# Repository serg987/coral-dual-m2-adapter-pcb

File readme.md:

# Dual Coral TPU m.2 E key to NVME m.2 M key adapter

## Overview

Simple adapter to install up to 2 dual Coral TPU modules in m.2 E key format to m.2 M key 2280 nvme slot.
Single E key Coral modules and a combination of single and dual ones should work as well.
The idea was to create a simple and affordable adapter on a two-layer PCB that can be soldered without 
any special equipment and professional soldering skills. The drawback is that it relies on some specific 
hardware and components, but they are still relatively easy to purchase. Also it goes out of m.2 2280 slot dimensions
by 8 mm on the side of the secure screw.

Third-party references: M2 E-Key slot KiCad symbol and the footprint are taken from 
https://github.com/CRImier/MyKiCad/tree/master/Laptop%20mods with some adjustments.

## Get the PCB

You can order PCB from PBCway.com via this 
[link](https://www.pcbway.com/project/shareproject/Dual_Coral_TPU_m_2_E_key_to_NVME_m_2_M_key_adapter_e422809f.html). 
Buying it from PCBway (should be around $10 including delivery to the US) you would support the Author in his 
future development.

### Gerbers

Gerber files are not provided. To get them, open the Kicad project and export them. 

## Hardware and schematics

The main part is m.2 M key expansion board based on the ASM1184E chip. It splits 1 PCIE lane into 4 single ones. It 
affects the speed, but for this specific application, the PCIE speed affects only a little. The adapter is connected to 
this board with 4 USB-3 Type A male connectors. The adapter has its power supply and needs an external power source of
5-12V. The adapter's PCB is installed above the expansion board as a sandwich, having an overall height of about 25 mm 
without Coral heat sink. The dimensions allow installation into the Dell Micro 50XX/70XX case, but without a heatsink, 
so it may have issues with heat dissipation there. The author used a Chatreey iT12 mini-pc which is available on 
Aliexpress without its bottom cover. The adapter hangs over m.2 2280 secure screw by around 8 mm. But in most cases, 
it should not be an issue.

An example of the adapter installed in the Dell Micro case (here and in some other pictures is the first version of the 
adapter that has a slightly different layout, but the same dimensions):

An example of the adapter installed in Chatreey iT12 mini-pc case:

### PCIE connections

Pretty straightforward. A few lanes are swapped to make it easier to trace the PCB. CLKREQ# pins are connected to
pull-up resistors. PERST# pins are combined as the AS1184 board has them all connected. PEWAKE# pins are not used.

### Power supply

ASM1184 datasheet is not available, but it heats up very well suspiciously consuming a significant current.
4 TPUs may consume around 6W, so it may be not enough for a m2 socket to handle that power. That's why a
separate power supply is introduced for Coral modules. It can be supplied from a 5 to 12 V power source.
It is based on the FR9889 chip and has the following schematics:

According to datasheet, R4 + R5 both should be 26.2 kOhm, but it can be something in between of 25.5 to 27.0 kOhm

The full schematics in PDF is [here](media/schematics.pdf) 

### Heat dissipation

ASM1184 board comes with its heatsink. Four Coral TPUs are heated up pretty quickly, so it is _necessary_ to have a 
heatsink for them as well. The author used a standard m2 SSD heatsink with a 1.0 mm thermal pad were secured by 2 
rubber rings.

## PCB layouts

Front:

Bottom:

Again, you can order PCBs 
[here](https://www.pcbway.com/project/shareproject/Dual_Coral_TPU_m_2_E_key_to_NVME_m_2_M_key_adapter_e422809f.html)

## Parts and materials

| Part                                     | Picture                                                                                              | Link to buy                                                                                                                                                                                                                                                                                    | Comments                                                                                                                                                         |
|------------------------------------------|------------------------------------------------------------------------------------------------------|------------------------------------------------------------------------------------------------------------------------------------------------------------------------------------------------------------------------------------------------------------------------------------------------|------------------------------------------------------------------------------------------------------------------------------------------------------------------|
| m.2 M key PCIE expansion card            |                        | [Aliexpress1](https://www.aliexpress.us/item/3256806084552405.html) <br/>[Aliexpress2](https://www.aliexpress.us/item/3256804686887041.html) <br/>[Aliexpress3](https://www.aliexpress.us/item/3256805414546446.html)<br/> [Aliexpress4](https://www.aliexpress.us/item/3256804977336000.html) | Many of them, search by 'ASM1184 m2' on other marketplaces                                                                                                       |
| USB3 type A through hole male connector  |                                        | [Aliexpress](https://www.aliexpress.us/item/3256802702094978.html)<br/> [Alibaba in bulk (>1000)](https://www.alibaba.com/product-detail/China-Factory-3-0-USB-Male_1600279588022.html)                                                                                                        | The most rare part. Found only in one shop on Aliexpress. But they are still available                                                                           |
| m.2 E key slot.<br/>H>4.2 mm             |           | [Aliexpress1](https://www.aliexpress.us/item/3256804027556698.html) <br/>[Aliexpress2](https://www.aliexpress.us/item/3256804027422044.html) <br/>[Aliexpress3](https://www.aliexpress.us/item/3256803741249397.html)                                                                          | Minimal height is 4.2 mm! Otherwise Coral PCB components will touch adapter's PCB components                                                                     |
| FR9889                                   |                                                                                                      |                                                                                                                                                                                                                                                                                                | Easy to find, has a bottom pad, so requires a air soldering gun. Was not tested, but FR9888, FR9887, and FR9886 should work as well as they have the same pinout |
| R1-R9, C1-C11,D1                         |                                                                                                      |                                                                                                                                                                                                                                                                                                | 1206 SMD components, no specific requirements; may use 0603 and 0805 sizes as well                                                                               |
| L1 1040 10uH inductor                    |                                                                                                      | [Aliexpress1](https://www.aliexpress.us/item/3256806022025333.html) <br/>[Aliexpress2](https://www.aliexpress.us/item/3256802793808255.html) <br/>[Aliexpress2](https://www.aliexpress.us/item/3256805451423156.html)                                                                          | Not recommended to use sizes smaller than 1040 as they have limited current                                                                                      |
| JST SH 6p male connector SMD             |                                                                                                      | [male + female + wires set, Ali](https://www.aliexpress.us/item/3256805451423156.html)<br/>[same](https://www.aliexpress.us/item/3256805601260635.html)                                                                                                                                        | should be SMD and SH (1.0 mm pitch)                                                                                                                              |
| M2 standoffs: 17 and 2 or 3 mm in height |  | [Aliexpress1](https://www.aliexpress.us/item/3256802766024100.html) <br/>[Aliexpress2](https://www.aliexpress.us/item/3256805275813321.html) <br/>[Aliexpress3](https://www.aliexpress.us/item/3256805110491444.html) <br/>[Aliexpress4](https://www.aliexpress.us/item/3256805863280885.html) | Optional; 2 mm for 4.2 mm m.2 E key slot and 3 mm for 4.8 mm m.2 E key slot                                                                                      |

A connector to whatever power source of 5-12V in your setup is not included in this list.
The easiest way to get the power in a real system - find a SATA power supply connector, usually it is available 
even in mini-pcs.

## Assembling

Whatever is possible and convenient, perhaps:

Solder M2 connectors as it is the hardest and the most tedious work. It is possible with only soldering iron having a 
sharp tip, there are guidances on the Internet

Important! After soldering double check there are no interconnected and not connected pins.

Solder FR9889 IC (or its analog, may require an air gun if it has a bottom pad, FR9887, and FR9886 in SOP-8 (NOT EP!) 
package should not have it), then solder all the front components

Solder all the bottom components

Make a power cable to your power source. All 3 GND and 3 Power pins should be connected due to the limited current load 
of JST SH connector. 

Connect it to the power sorce and check if 3.3V is generated and applied to all the m2 slots. If not - troubleshoot it.

The most critical part. Insert all the USB3 connectors in the expansion card

And then gently insert their pins into the adapter PCB.

Solder them, but do not push much on the PCB as it may end up bent. 

Gently remove the adapter PCB from the expansion card. 4 USB connectors hold it very strong, so just be careful and 
do not apply extra force.

Remove extra soldering flux even if it is a 'no-clean' one.

[Optional] Screw in 17 mm M2 standoff. You will need to screw out a screw underneath the expansion card  

When you insert the adapter again, in the PC, you can screw in the small (2/3 mm standoff) that will hold both Coral 
modules

Another option - secure it with only a screw and two nuts - one is on the front side and another one is at the bottom.

## Installation

Installation is pretty straightforward. Install PCIE expansion PCB first, and secure it with a screw.
Holding the PCIE expansion PCB slowly and gently insert the adapter. If you use standoffs, you need to screw the small 
standoff and only after that insert Coral modules. If you secure Coral modules with a screw and a nut without a long 
standoff, you can insert the adapter with Corals installed. Hold the expansion PCB while inserting and pulling out the 
adapter. 4 USB3 connectors are sitting very tight, you can damage both PCBs if not holding them properly.

Connect the power source.

Turn on the machine, Coral TPU drivers should be installed before that.

Run `lspci` command on Linux or go to Device Manager in Windows. You should see all 4 TPUs available.

Freegate or Codeproject.ai can use 4 TPUs as well.

Add a heatsink after you check everything works. Will need to remove the Corals and insert them again.

## Known issues

- No USB3 through-hole connector footprint was found, so created its own one. It is not clear if it is suitable for 
automated assembly
- Silkscreen does not have electrolytic capacitor polarity
- A few m2 connector GND pins have traces between pins inside the footprint. Even if it has no electrical side effects,
it makes it a bit harder to solder

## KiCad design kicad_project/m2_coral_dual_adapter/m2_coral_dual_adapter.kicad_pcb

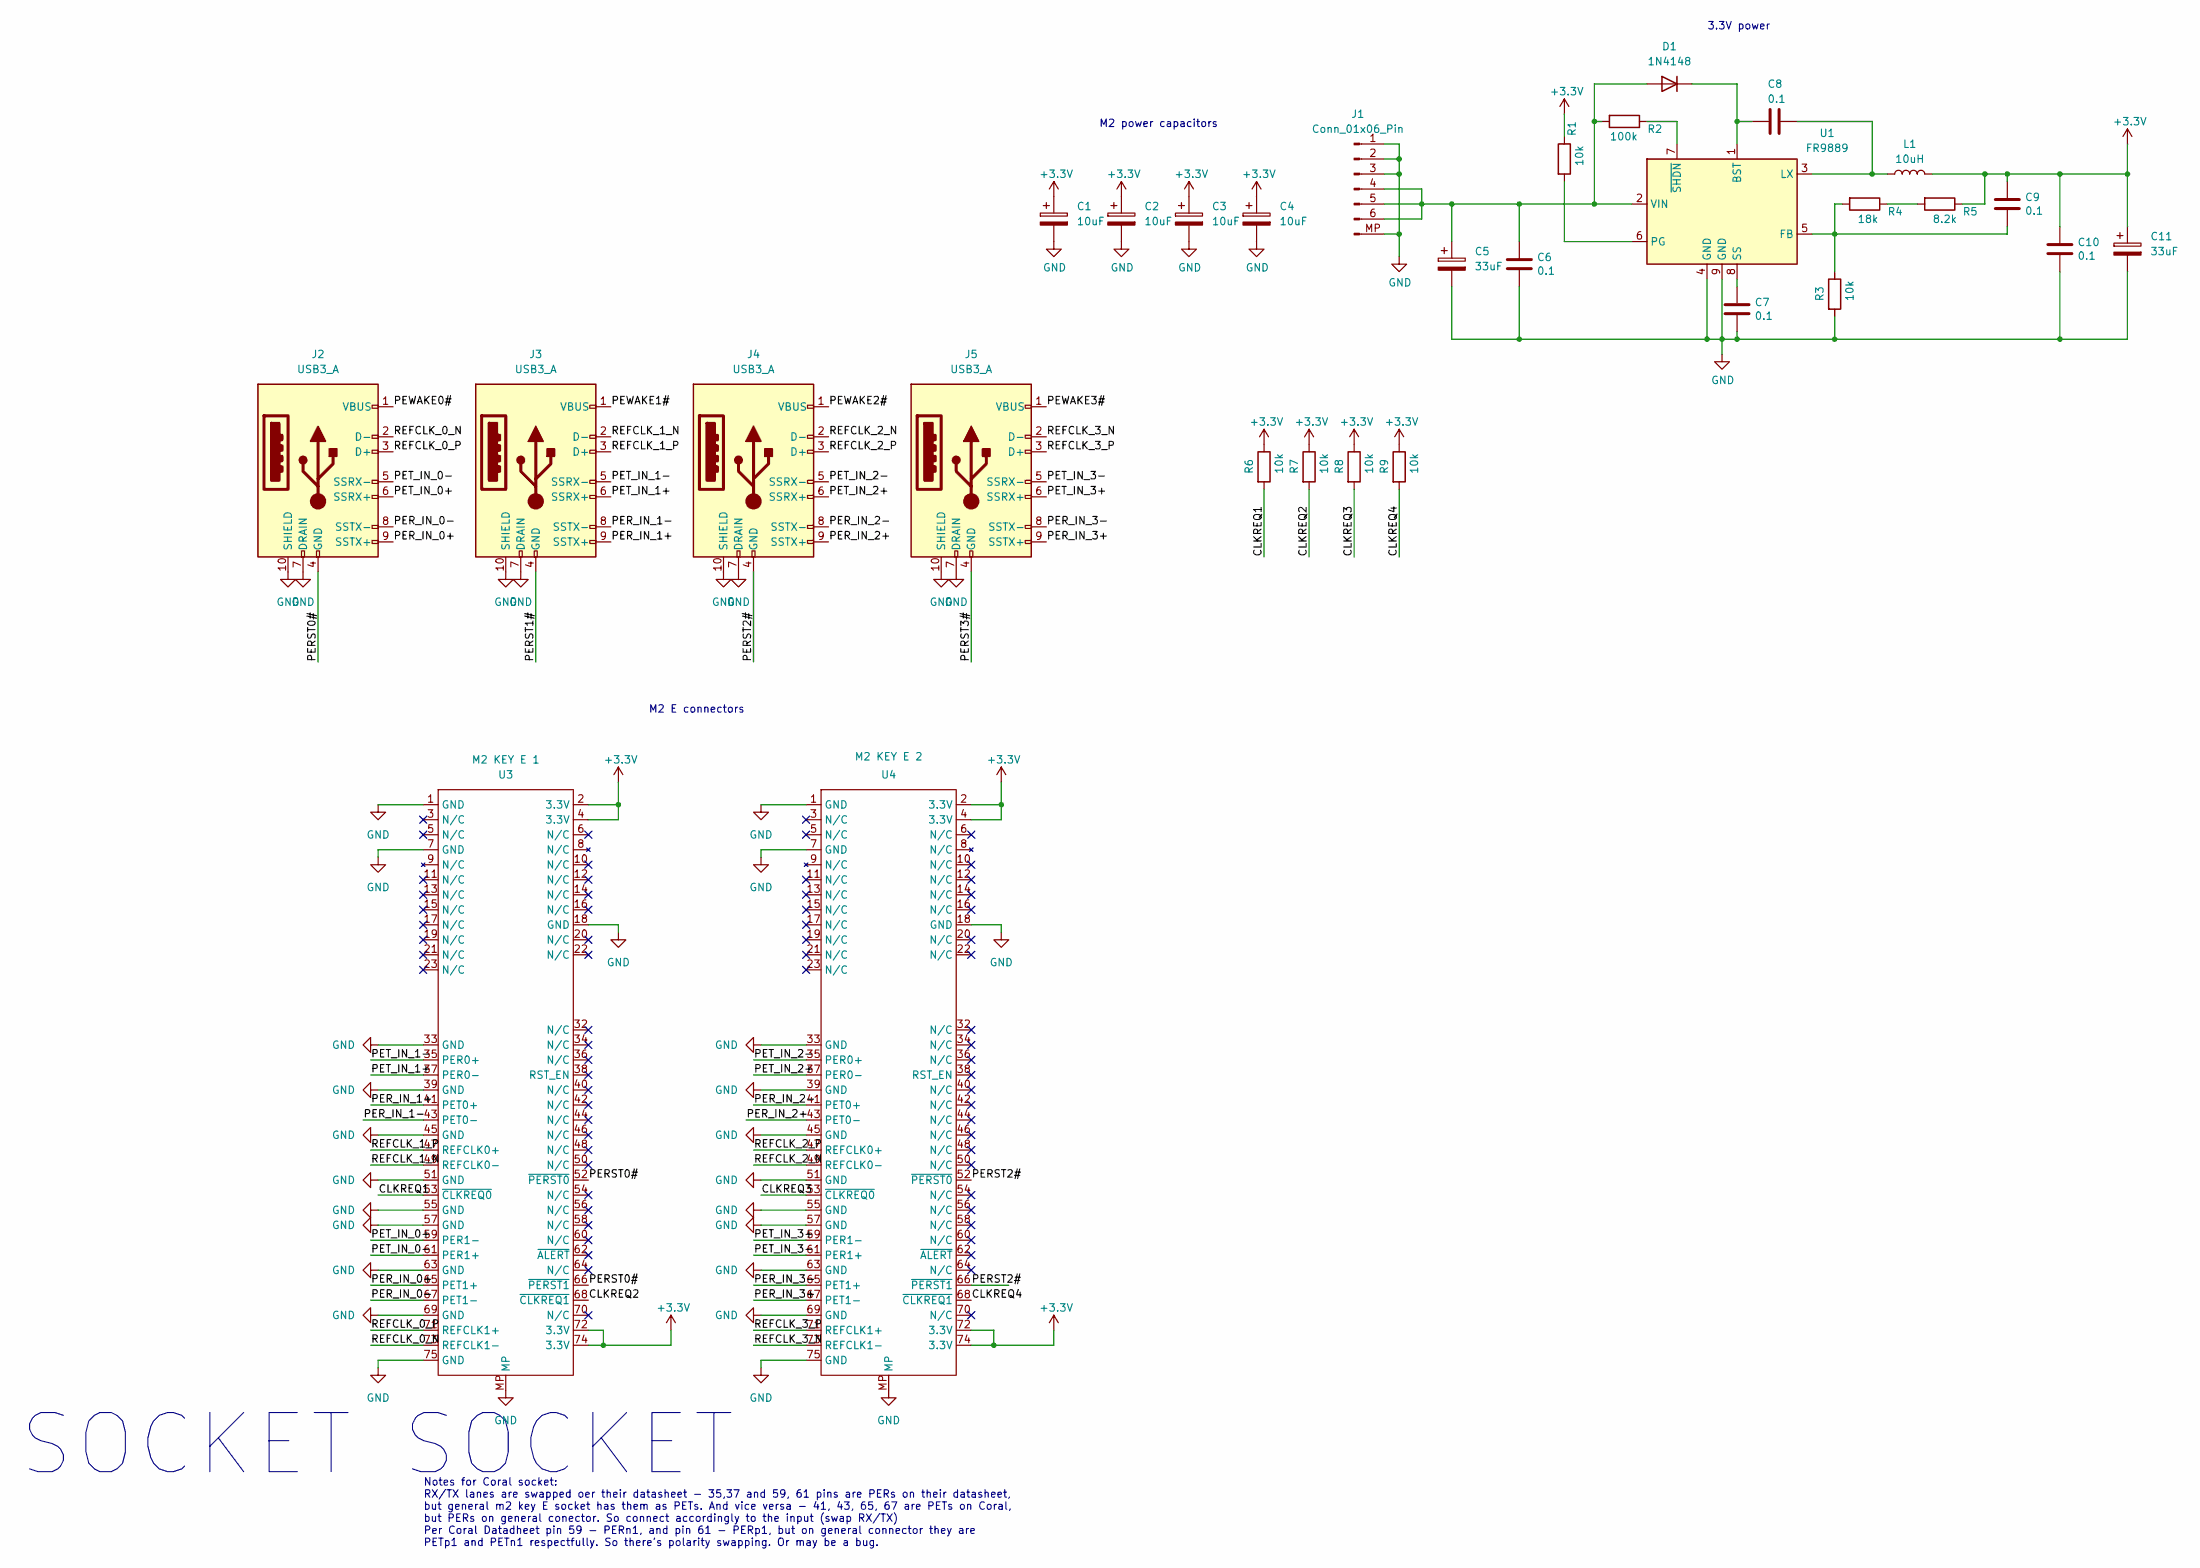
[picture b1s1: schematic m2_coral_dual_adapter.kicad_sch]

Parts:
C1, C2, C3, C4: 10uF; C_1206_3216Metric_Pad1.33x1.80mm_HandSolder
C5, C11: 33uF; C_1206_3216Metric_Pad1.33x1.80mm_HandSolder
C6, C7, C8, C9, C10: 0.1; C_1206_3216Metric_Pad1.33x1.80mm_HandSolder
D1: 1N4148; D_1206_3216Metric_Pad1.42x1.75mm_HandSolder
J1: Conn_01x06_Pin; JST_SH_SM06B-SRSS-TB_1x06-1MP_P1.00mm_Horizontal
J2, J3, J4, J5: USB3_A; USB_A_Male_vertical_v2
L1: 10uH; L_Wuerth_HCI-1040
R1, R3, R6, R7, R8, R9: 10k; R_1206_3216Metric_Pad1.30x1.75mm_HandSolder
R2: 100k; R_1206_3216Metric_Pad1.30x1.75mm_HandSolder
R4: 18k; R_1206_3216Metric_Pad1.30x1.75mm_HandSolder
R5: 8.2k; R_1206_3216Metric_Pad1.30x1.75mm_HandSolder
U1: FR9889; HSOP-8-1EP_3.9x4.9mm_P1.27mm_EP2.41x3.1mm_ThermalVias
U3: M2 KEY E 1; Conn_TE-M.2-0.5-67P-doublesided_TypeE
U4: M2 KEY E 2; Conn_TE-M.2-0.5-67P-doublesided_TypeE

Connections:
+3V3: C1.1, C2.1, C3.1, C4.1, C9.1, C10.1, C11.1, L1.2, R1.1, R5.1, R6.1, R7.1, R8.1, R9.1, U3.2 (3.3V), U3.4 (3.3V), U3.72 (3.3V), U3.74 (3.3V), U4.2 (3.3V), U4.4 (3.3V), U4.72 (3.3V), U4.74 (3.3V)
/CLKREQ1: R6.2, U3.53 (~CLKREQ0)
/CLKREQ2: R7.2, U3.68 (~CLKREQ1)
/CLKREQ3: R8.2, U4.53 (~CLKREQ0)
/CLKREQ4: R9.2, U4.68 (~CLKREQ1)
/PERST0#: J2.4 (GND), U3.52 (~PERST0), U3.66 (~PERST1)
/PERST1#: J3.4 (GND)
/PERST2#: J4.4 (GND), U4.52 (~PERST0), U4.66 (~PERST1)
/PERST3#: J5.4 (GND)
/PER_IN_0+: J2.9 (SSTX+), U3.65 (PET1+)
/PER_IN_0-: J2.8 (SSTX-), U3.67 (PET1-)
/PER_IN_1+: J3.9 (SSTX+), U3.41 (PET0+)
/PER_IN_1-: J3.8 (SSTX-), U3.43 (PET0-)
/PER_IN_2+: J4.9 (SSTX+), U4.43 (PET0-)
/PER_IN_2-: J4.8 (SSTX-), U4.41 (PET0+)
/PER_IN_3+: J5.9 (SSTX+), U4.67 (PET1-)
/PER_IN_3-: J5.8 (SSTX-), U4.65 (PET1+)
/PET_IN_0+: J2.6 (SSRX+), U3.59 (PER1-)
/PET_IN_0-: J2.5 (SSRX-), U3.61 (PER1+)
/PET_IN_1+: J3.6 (SSRX+), U3.37 (PER0-)
/PET_IN_1-: J3.5 (SSRX-), U3.35 (PER0+)
/PET_IN_2+: J4.6 (SSRX+), U4.37 (PER0-)
/PET_IN_2-: J4.5 (SSRX-), U4.35 (PER0+)
/PET_IN_3+: J5.6 (SSRX+), U4.59 (PER1-)
/PET_IN_3-: J5.5 (SSRX-), U4.61 (PER1+)
/PEWAKE0#: J2.1 (VBUS)
/PEWAKE1#: J3.1 (VBUS)
/PEWAKE2#: J4.1 (VBUS)
/PEWAKE3#: J5.1 (VBUS)
/REFCLK_0_N: J2.2 (D-), U3.73 (REFCLK1-)
/REFCLK_0_P: J2.3 (D+), U3.71 (REFCLK1+)
/REFCLK_1_N: J3.2 (D-), U3.49 (REFCLK0-)
/REFCLK_1_P: J3.3 (D+), U3.47 (REFCLK0+)
/REFCLK_2_N: J4.2 (D-), U4.49 (REFCLK0-)
/REFCLK_2_P: J4.3 (D+), U4.47 (REFCLK0+)
/REFCLK_3_N: J5.2 (D-), U4.73 (REFCLK1-)
/REFCLK_3_P: J5.3 (D+), U4.71 (REFCLK1+)
GND: C1.2, C2.2, C3.2, C4.2, C5.2, C6.2, C7.2, C10.2, C11.2, J1.1, J1.2, J1.3, J1.MP (GND), J2.7 (DRAIN), J2.10 (SHIELD), J3.7 (DRAIN), J3.10 (SHIELD), J4.7 (DRAIN), J4.10 (SHIELD), J5.7 (DRAIN), J5.10 (SHIELD), R3.2, U1.4 (GND), U1.9 (GND), U3.1 (GND), U3.7 (GND), U3.18 (GND), U3.33 (GND), U3.39 (GND), U3.45 (GND), U3.51 (GND), U3.55 (GND), U3.57 (GND), U3.63 (GND), U3.69 (GND), U3.75 (GND), U3.MP, U4.1 (GND), U4.7 (GND), U4.18 (GND), U4.33 (GND), U4.39 (GND), U4.45 (GND), U4.51 (GND), U4.55 (GND), U4.57 (GND), U4.63 (GND), U4.69 (GND), U4.75 (GND), U4.MP
unnamed: C5.1, C6.1, D1.2 (A), J1.4, J1.5, J1.6, R2.2, U1.2 (VIN)
unnamed: C8.1, D1.1 (K), U1.1 (BST)
unnamed: R4.1, R5.2
unnamed: C9.2, R3.1, R4.2, U1.5 (FB)
unnamed: C8.2, L1.1, U1.3 (LX)
unnamed: R1.2, U1.6 (PG)
unnamed: C7.1, U1.8 (SS)
unnamed: R2.1, U1.7 (~SHDN)

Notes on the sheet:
Notes for Coral socket: RX/TX lanes are swapped oer their datasheet - 35,37 and 59, 61 pins are PERs on their datasheet, but general m2 key E socket has them as PETs. And vice versa - 41, 43, 65, 67 are PETs on Coral, but PERs on general conector. So connect accordingly to the input (swap RX/TX) Pe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
SOCKET
3.3V power
M2 E connectors
M2 power capacitors

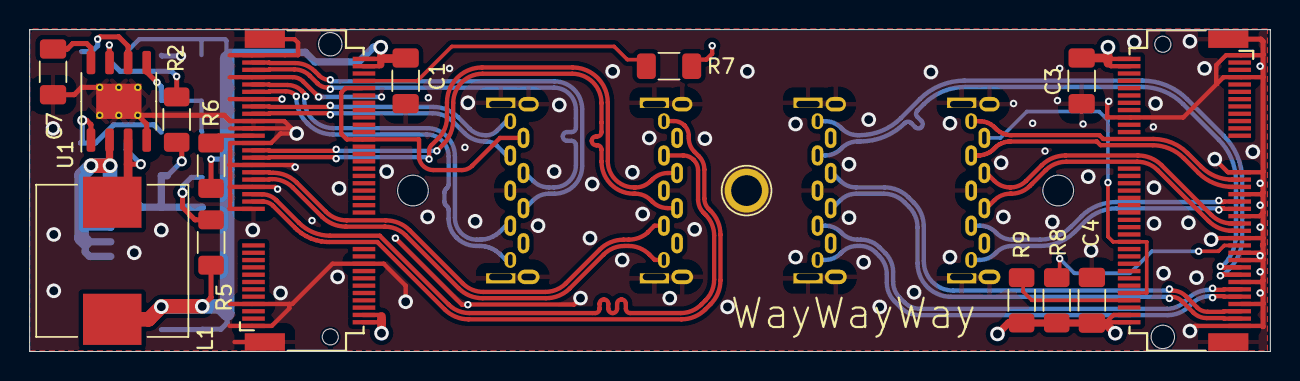
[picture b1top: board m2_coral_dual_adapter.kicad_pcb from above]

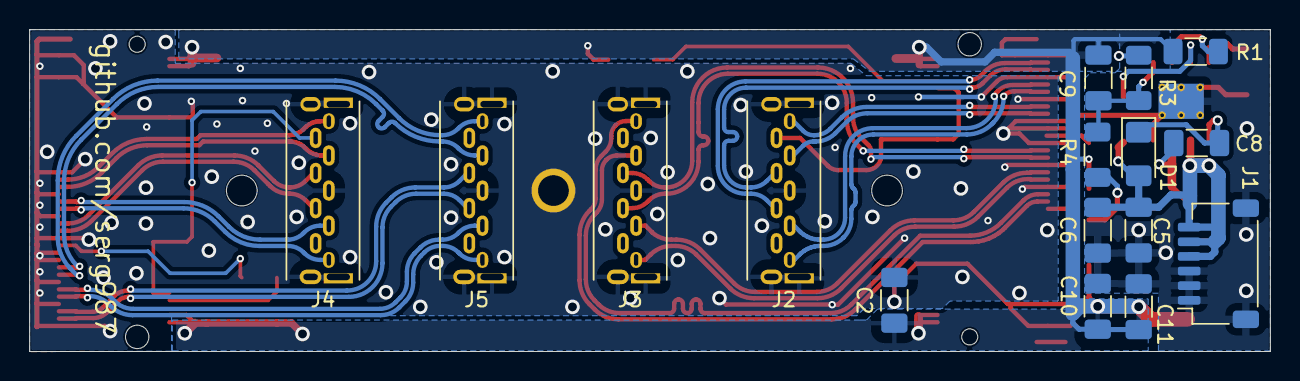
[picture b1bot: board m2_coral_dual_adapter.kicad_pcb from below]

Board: 2 copper layers, 84.8 x 22.0 mm, 30 parts (16 on the bottom side), 40 nets.

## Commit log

2024-07-04 Add links to order pcbs
2024-07-04 Add GPLv3 licence
